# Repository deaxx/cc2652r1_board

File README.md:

# cc2652r1_board
mini-dev board on RF-BM-2652B1

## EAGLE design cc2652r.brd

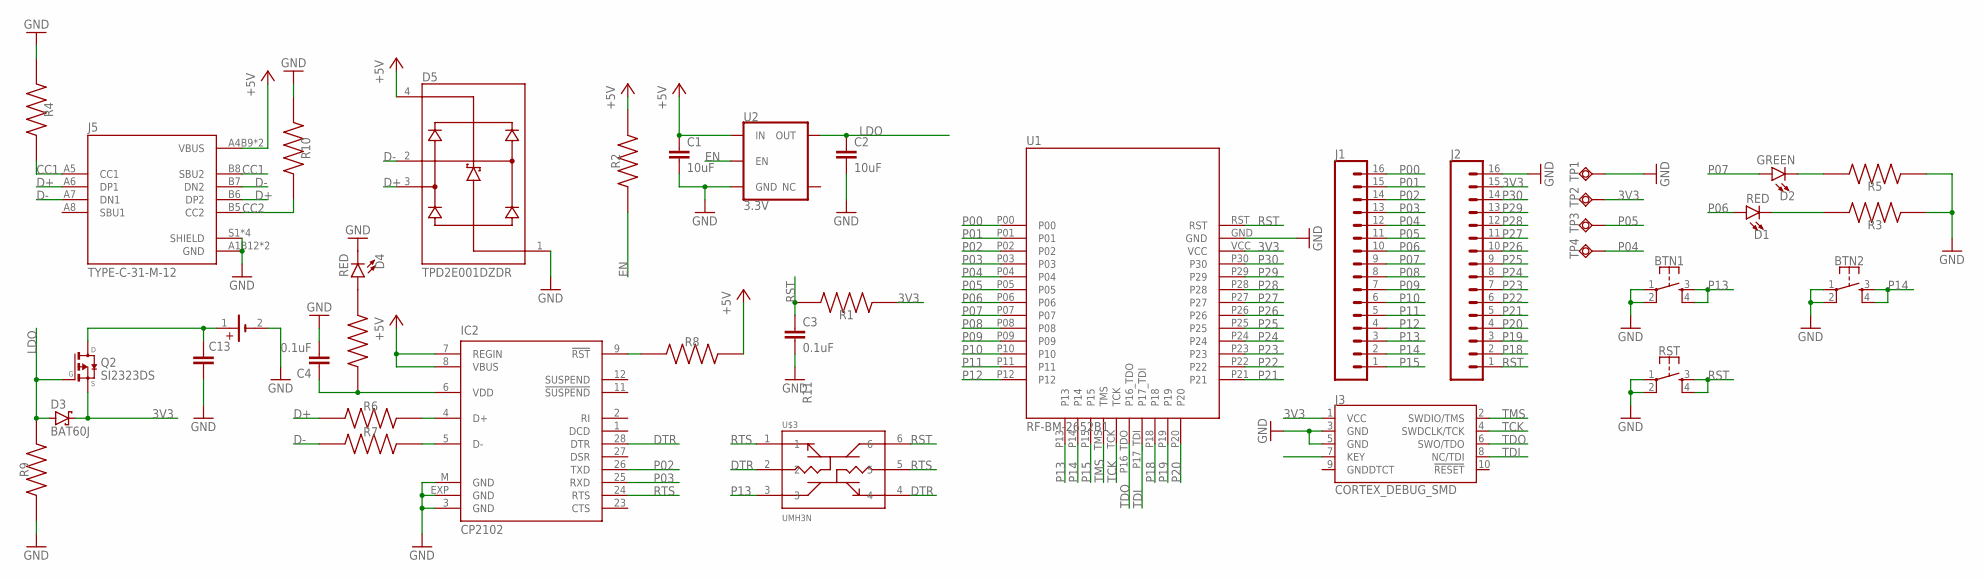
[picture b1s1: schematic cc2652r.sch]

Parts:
BT2: 79527141
BTN1, BTN2: MOMENTARY-SWITCH-SPST-2-SMD-4.6X2.8MM; TACTILE_SWITCH_SMD_4.6X2.8MM
C1, C2: 10uF; 0603
C3, C4: 0.1uF; 0603
C13: C_TANTALUM-2917(7343-METRIC); CAPM7343X310
D1, D4: RED; LED-0603
D2: GREEN; LED-0603
D3: BAT60J; SOD323_ST
D5: TPD2E001DZDR; SOT192P237X122-4N
IC2: CP2102; MLP28
J1, J2: CONN_161X16_NO_SILK; 1X16_NO_SILK
J3: CORTEX_DEBUG_SMD; SAMTECH_FTSH-105-01
J5: TYPE-C-31-M-12; HRO_TYPE-C-31-M-12
Q2: SI2323DS; SOT23
R1, R2, R3, R4, R5, R6, R7, R8, R9, R10, R11: RC0402FR-073M6L; RESC1005X40N
RST: MOMENTARY-SWITCH-SPST-2-SMD-4.6X2.8MM; TACTILE_SWITCH_SMD_4.6X2.8MM
TP1, TP2, TP3, TP4: TPSQTP14R; TP14R
U1: RF-BM-2652B1
U2: 3.3V; SOT23-5
U$3: UMH3N; SOP65P210X100-6N

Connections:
3V3: D3.C, J2.15, J3.1 (VCC), Q2.2 (S), R1.1, TP2.TP, U1.VCC
+5V: C1.1, D5.4 (VCC), IC2.7 (REGIN), IC2.8 (VBUS), J5.A4B9 (VBUS), J5.B4A9 (VBUS), R2.2, R8.2, U2.1 (IN)
CC1: J5.A5 (CC1), J5.B8 (SBU2), R4.2
CC2: J5.B5 (CC2), R10.2
D+: D5.3 (IO2), J5.A6 (DP1), J5.B6 (DP2), R6.1
D-: D5.2 (IO1), J5.A7 (DN1), J5.B7 (DN2), R7.1
DTR: IC2.28 (DTR), U$3.2, U$3.4
EN: R2.1, U2.3 (EN)
GND: BT2.2 (-), BTN1.1, BTN1.2, BTN2.1, BTN2.2, C1.2, C2.2, C3.2, C4.2, C13.2, D4.C, D5.1 (GND), IC2.3 (GND), IC2.EXP (GND), IC2.M (GND), J2.16, J3.3 (GND), J3.5 (GND), J5.A1B12 (GND), J5.B1A12 (GND), J5.S1 (SHIELD), J5.S2 (SHIELD), J5.S3 (SHIELD), J5.S4 (SHIELD), R3.1, R4.1, R5.1, R9.1, R10.1, RST.1, RST.2, TP1.TP, U1.GND, U2.2 (GND)
LDO: C2.1, D3.A, Q2.1 (G), R9.2, U2.5 (OUT)
unnamed: IC2.9 (!RST), R8.1
unnamed: D1.C, R3.2
unnamed: D2.C, R5.2
unnamed: IC2.4 (D+), R6.2
unnamed: IC2.5 (D-), R7.2
unnamed: BT2.1 (+), C13.1, Q2.3 (D)
unnamed: D4.A, R11.1
P00: J1.16, U1.P00
P01: J1.15, U1.P01
P02: IC2.26 (TXD), J1.14, U1.P02
P03: IC2.25 (RXD), J1.13, U1.P03
P04: J1.12, TP4.TP, U1.P04
P05: J1.11, TP3.TP, U1.P05
P06: D1.A, J1.10, U1.P06
P07: D2.A, J1.9, U1.P07
P08: J1.8, U1.P08
P09: J1.7, U1.P09
P10: J1.6, U1.P10
P11: J1.5, U1.P11
P12: J1.4, U1.P12
P13: BTN1.3, BTN1.4, J1.3, U1.P13, U$3.3
P14: BTN2.3, BTN2.4, J1.2, U1.P14
P15: J1.1, U1.P15
P18: J2.2, U1.P18
P19: J2.3, U1.P19
P20: J2.4, U1.P20
P21: J2.5, U1.P21
P22: J2.6, U1.P22
P23: J2.7, U1.P23
P24: J2.8, U1.P24
P25: J2.9, U1.P25
P26: J2.10, U1.P26
P27: J2.11, U1.P27
P28: J2.12, U1.P28
P29: J2.13, U1.P29
P30: J2.14, U1.P30
RST: C3.1, J2.1, R1.2, RST.3, RST.4, U1.RST, U$3.6
RTS: IC2.24 (RTS), U$3.1, U$3.5
TCK: J3.4 (SWDCLK/TCK), U1.TCK
TDI: J3.8 (NC/TDI), U1.P17_TDI
TDO: J3.6 (SWO/TDO), U1.P16_TDO
TMS: J3.2 (SWDIO/TMS), U1.TMS
U3V3: C4.1, IC2.6 (VDD), R11.2

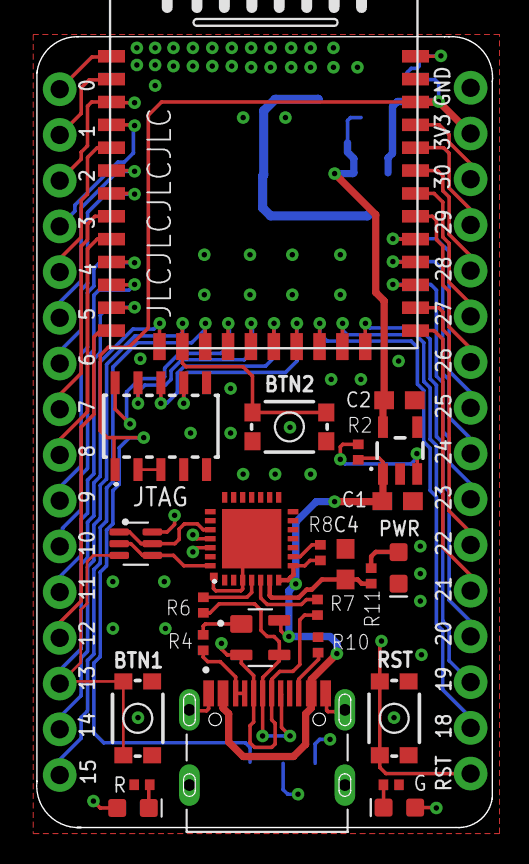
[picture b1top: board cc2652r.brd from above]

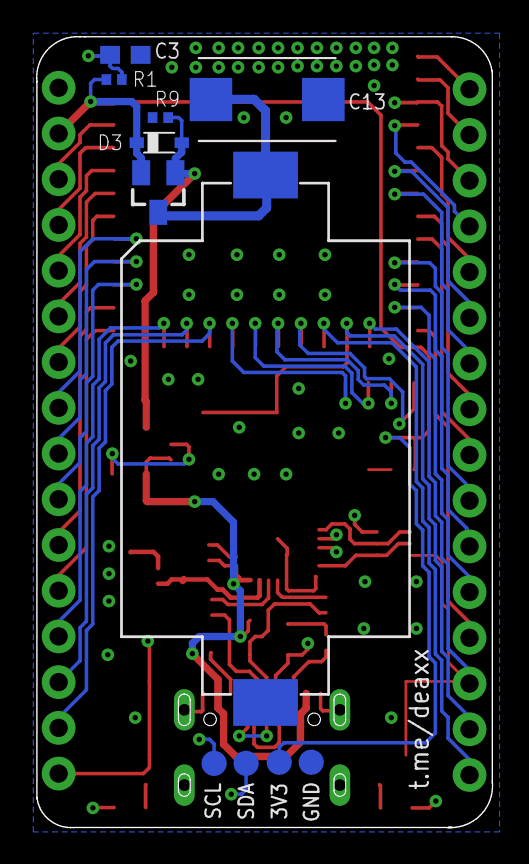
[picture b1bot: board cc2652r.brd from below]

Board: 4 copper layers, 25.3 x 43.9 mm, 38 parts (11 on the bottom side), 53 nets.

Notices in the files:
parts and their libraries:
SparkFun-Connectors: Licensing: Creative Commons ShareAlike 4.0 International - https://creativecommons.org/licenses/by-sa/4.0
